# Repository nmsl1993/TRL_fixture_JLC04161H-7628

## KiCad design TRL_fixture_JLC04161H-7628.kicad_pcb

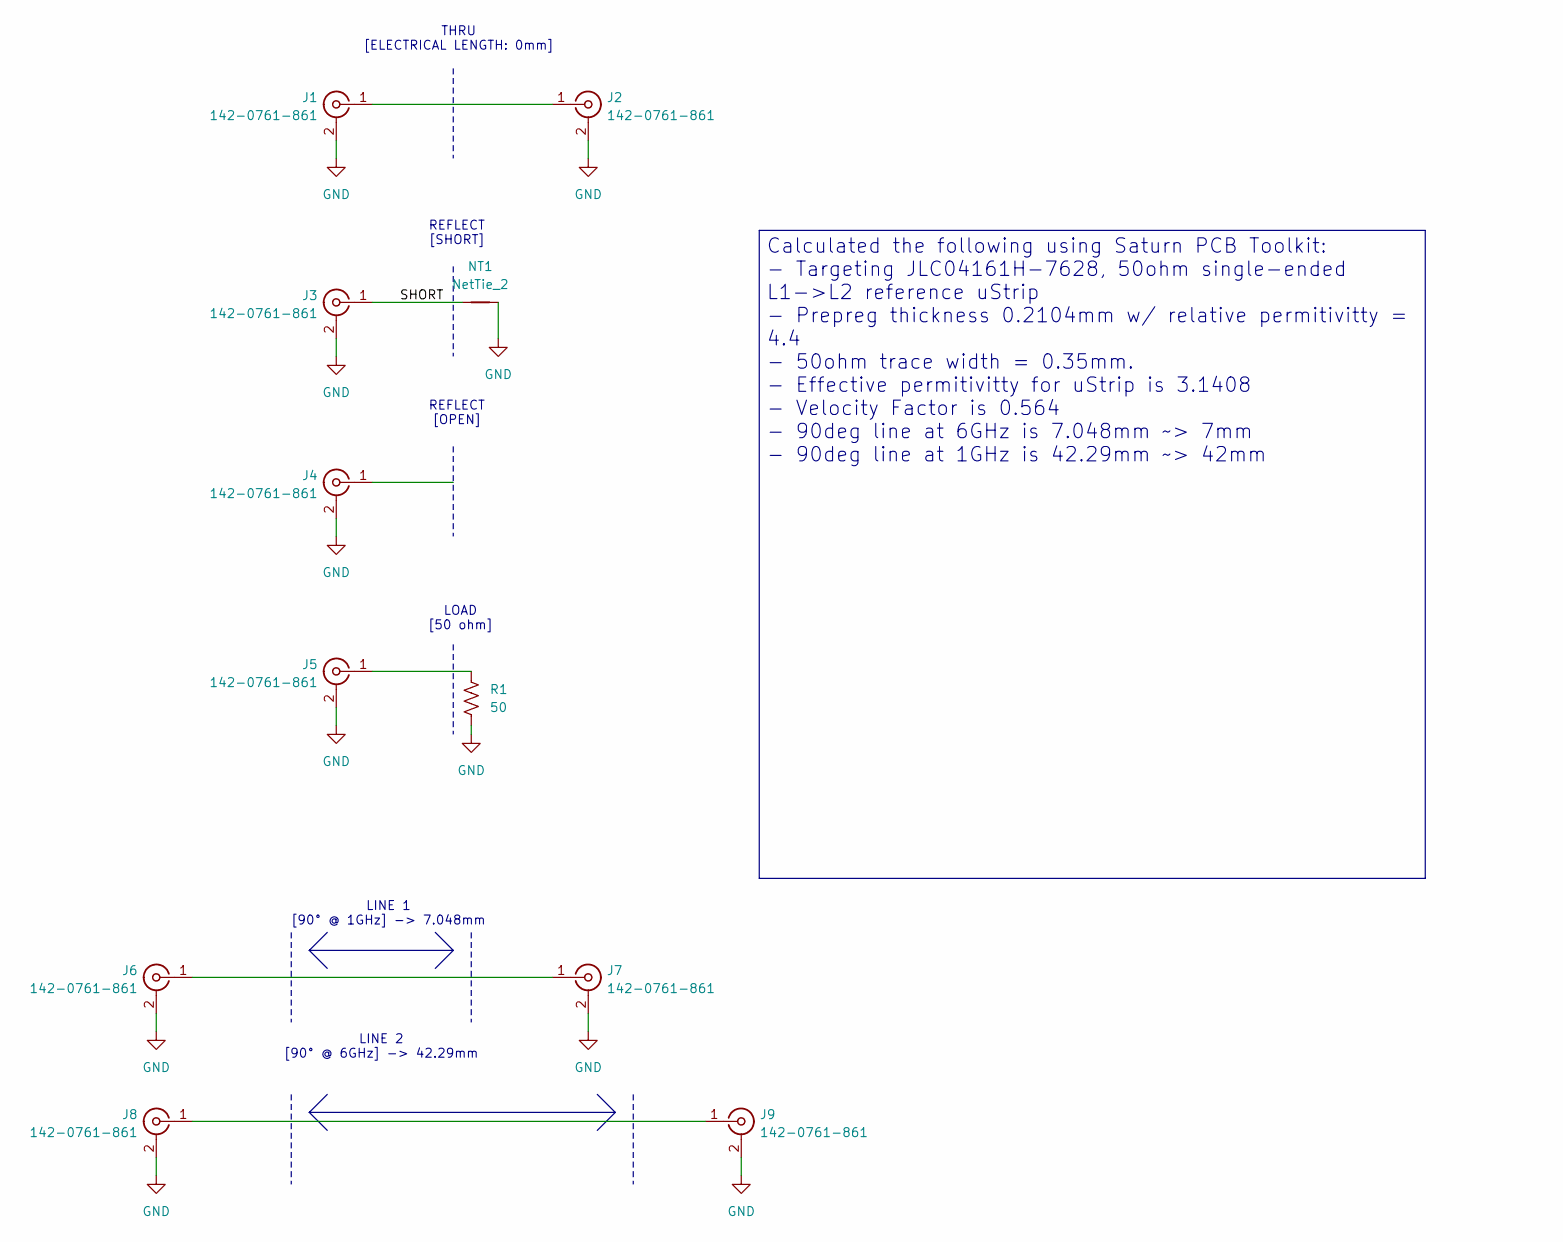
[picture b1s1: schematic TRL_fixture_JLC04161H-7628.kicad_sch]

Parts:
J1, J2, J3, J4, J5, J6, J7, J8, J9: 142-0761-861; Johnson_142-0761-861
NT1: NetTie_2; NetTie-2_SMD_Pad0.5mm
R1: 50; R_0402_1005Metric

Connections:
/SHORT: J3.1 (In), NT1.2
GND: J1.2 (Ext), J2.2 (Ext), J3.2 (Ext), J4.2 (Ext), J5.2 (Ext), J6.2 (Ext), J7.2 (Ext), J8.2 (Ext), J9.2 (Ext), NT1.1, R1.2
unnamed: J1.1 (In), J2.1 (In)
unnamed: J5.1 (In), R1.1
unnamed: J6.1 (In), J7.1 (In)
unnamed: J8.1 (In), J9.1 (In)

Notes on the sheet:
LOAD [50 ohm]
LINE 1 [90° @ 1GHz] -> 7.048mm
THRU [ELECTRICAL LENGTH: 0mm]
REFLECT [SHORT]
REFLECT [OPEN]
LINE 2 [90° @ 6GHz] -> 42.29mm
Calculated the following using Saturn PCB Toolkit: - Targeting JLC04161H-7628, 50ohm single-ended L1->L2 reference uStrip - Prepreg thickness 0.2104mm w/ relative permitivitty = 4.4 - 50ohm trace width = 0.35mm. - Effective permitivitty for uStrip is 3.1408 - Velocity Factor is 0.564 - 90deg line a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

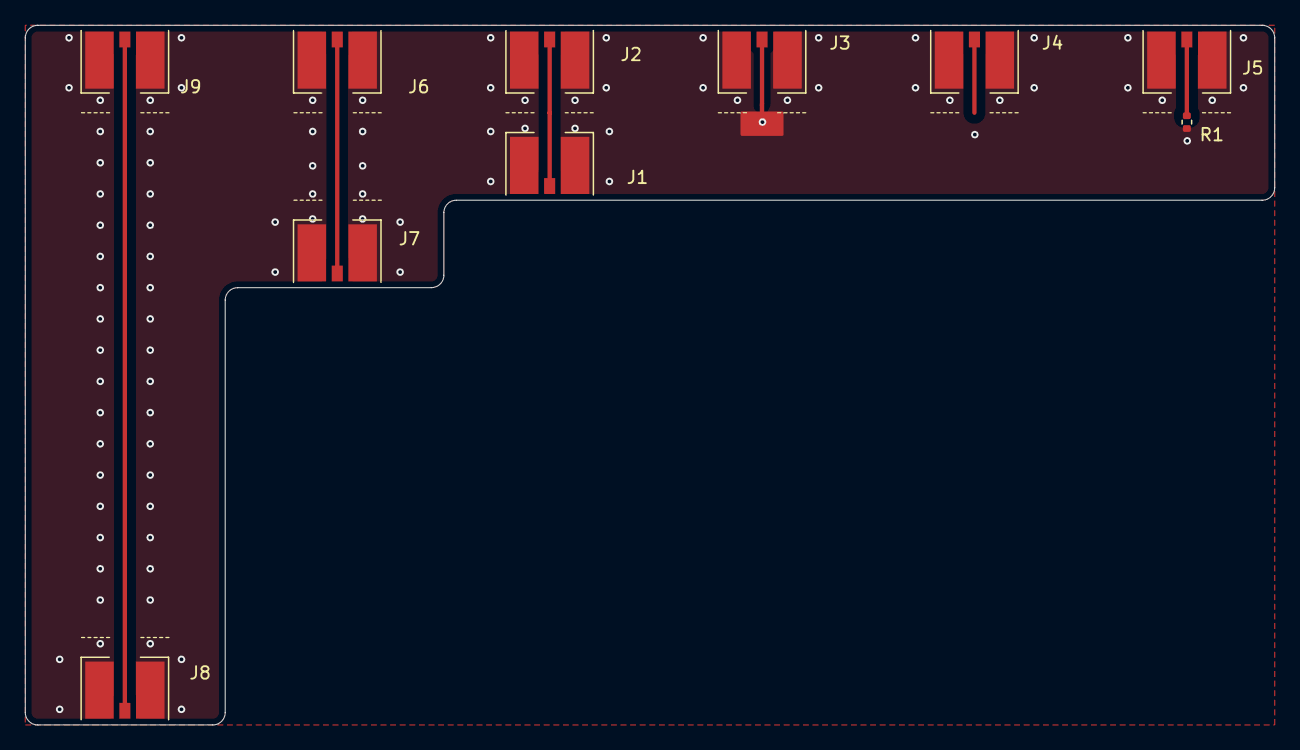
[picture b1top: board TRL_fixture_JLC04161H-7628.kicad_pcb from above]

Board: 4 copper layers, 100.0 x 56.0 mm, 11 parts (0 on the bottom side), 6 nets.

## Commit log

2025-07-15 Initial commit, not yet passing DRC
2025-07-17 TRL fixture DRC clean
2025-07-17 Added as-submitted gerbers to JLC
